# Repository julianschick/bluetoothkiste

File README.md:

# Bluetoothkiste

Bluetooth-Box für Segelflugzeuge zur Kommunikation zwischen Smartphone (mit beispielsweise XCSoar) und LX (5000/7000/7007) sowie FLARM. LX und FLARM senden über zwei getrennte Bluetooth-Module, werden also als zwei unterschiedliche Serialports auf dem Smartphone sichtbar. Das FLARM wird über den breiten RJ45-Westernstecker an die Box angeschlossen und wird auch über die Box mit Strom versorgt. Das LX wird über die 9-polige D-Sub-Schnittstelle, die meistens mit _PC_ oder _Kolibri_ beschriftet ist, angeschlossen. Eine USB-Buchse kann zusätzlich nach außen gelegt werden, um eine 5V-Stromversorgung im Cockpit zu ermöglichen. Die Datenpins sind nicht angeschlossen.

Die Verbindung zum Flarm kann über Jumper so eingestellt werden, dass keine Daten ans Flarm gesendet werden. Das ist nützlich, wenn man mehrere Bluetooth-Boxen an ein Flarm anschließen will. Die RX- und TX-Leitung zum LX kann per Jumper auf den RS232-Pins 2 und 3 frei konfiguriert werden. Das ist notwendig, da die RX-/TX-Pins vertauscht sind, je nachdem ob man die PC-Schnittstelle (u. U. mit Adapterkabel vom 5-poligen Binderstecker) oder die Kolibri-Schnittstelle verwendet. Im Zweifelsfall durchmessen, auf welchem Pin das Gerät spricht.

Ein Gehäuse, das mit dem 3D-Drucker ausgedruckt werden kann, ist ebenfalls im Repository zu finden. Bilder siehe unten.

## Teileliste

Mit passenden Artikelbezeichnungen für den Berliner Elektroteilehändler [Segor](https://www.segor.de).

Anzahl | Beschreibung | Segor-Artikelbezeichnung
--|--|--
1 | Gehäuse | *PP41 sw*
1 | USB-A-Buchse für Printmontage | *USB-A BU/V*
1 | RJ45-Buchse für Printmontage | *8P8C-BU/S 14mm*
1 | RS232-Converter | *MAX 232 N*
1 | D-Sub Buchse/Stecker 9-polig, Printmontage 90°, Abstand Pinreihe zu Steckerfläche 10mm | *DS09F-90°-10mm*/*DS09M-90°-10mm*
1 | Schaltregler | *R-78 5.0-1.0* oder (günstiger) *R-78E5.0-1.0*
1 | Sicherungshalter für Rundsicherungen, RM 5mm | *RSI-Halter/LP*
1 | Rundsicherung, RM 5mm | *RSI 2,0 A F oder RSI 2,0 A T (flink/träge)*
1 | Schraubklemmen, RM 5mm | *ARK 3 (RM 5mm)*
2 | Kondensator 10u, RM 5mm | *10u-R5.0-X7R/25V*
5 | Kondensator 1u, SMD-Bauform 1206 (3216 metrisch) | *1u0-1206-X7R/50V*
2 | Diode | *1N 5062*
2 | Bluetooth-Modul | *Bluetooth-Modul (HC-05/-06 oder ein HC-10-BLE-Modul)* [günstiger bei eBay!]
div. | Pinheader (je nach Anbringung der Bluetooth-Module)

## Wichtige Hinweise

* Je nachdem, wer zuletzt am Flugzeug rumgefrickelt hat, ist die D-Sub-Verbindung mal Male mal Female, am besten gleich das richtige Gegenstück auf die Platine löten.
* Die Bluetooth-Module können, wenn sie mit vertikalen Pinheader versehen sind, direkt reingesteckt werden (auf der Platine auch vertikale Pinheader anbringen). Sie sind dann vom Gehäusedeckel etwas vorgespannt. Bei eBay bekommt man i.d.R. Module mit 90° abgewinkelten Pinheader, diese kann man aber einfach umbiegen. Man kann sie auch direkt festlöten (ohne Female-Pinheader auf der Platine). Dabei stehen die Stifte nach unten weit aus der Platine heraus. Wenn man diese nicht abzwickt, kann man auch im Nachhinein noch per AT-Kommandos die Bluetooth-Module umkonfigurieren.
* Die Stromversorgung der Bluetooth-Module und des FLARM kann zusammengeschaltet werden per Jumper, wenn man nicht getrennt ein- und ausschalten möchte.
* Das FLARM muss extern abgesichert werden! Intern sind nur die Bluetooth-Module abgesichert.
* Darauf achten, den Schaltregler richtig herum zu montieren. Genauso den RS232-Chip.
* Darauf achten, die Bluetooth-Module richtig herum einzustecken.
* Die Bluetooth-Module müssen vor Benutzung per AT-Kommandos auf die richtige Baudrate eingestellt werden (FLARM meist 19200 und LX meist 4800). Name des Bluetoothgeräts und PIN können auch gesetzt werden. Damit man mit dem LX bidirektional kommunizieren kann, muss die Baudrate der PC-Verbindung des LX auf 4800 gesetzt werden. Das LX wirft seine NMEA-Daten immer mit 4800 Baud aus, kann aber mit konfigurierbarer Baudrate mit dem PC sprechen. Da das alles aber über das gleiche Bluetooth-Modul läuft, sollten 4800 Baud eingestellt sein.

## Bilder

## Gehäuse

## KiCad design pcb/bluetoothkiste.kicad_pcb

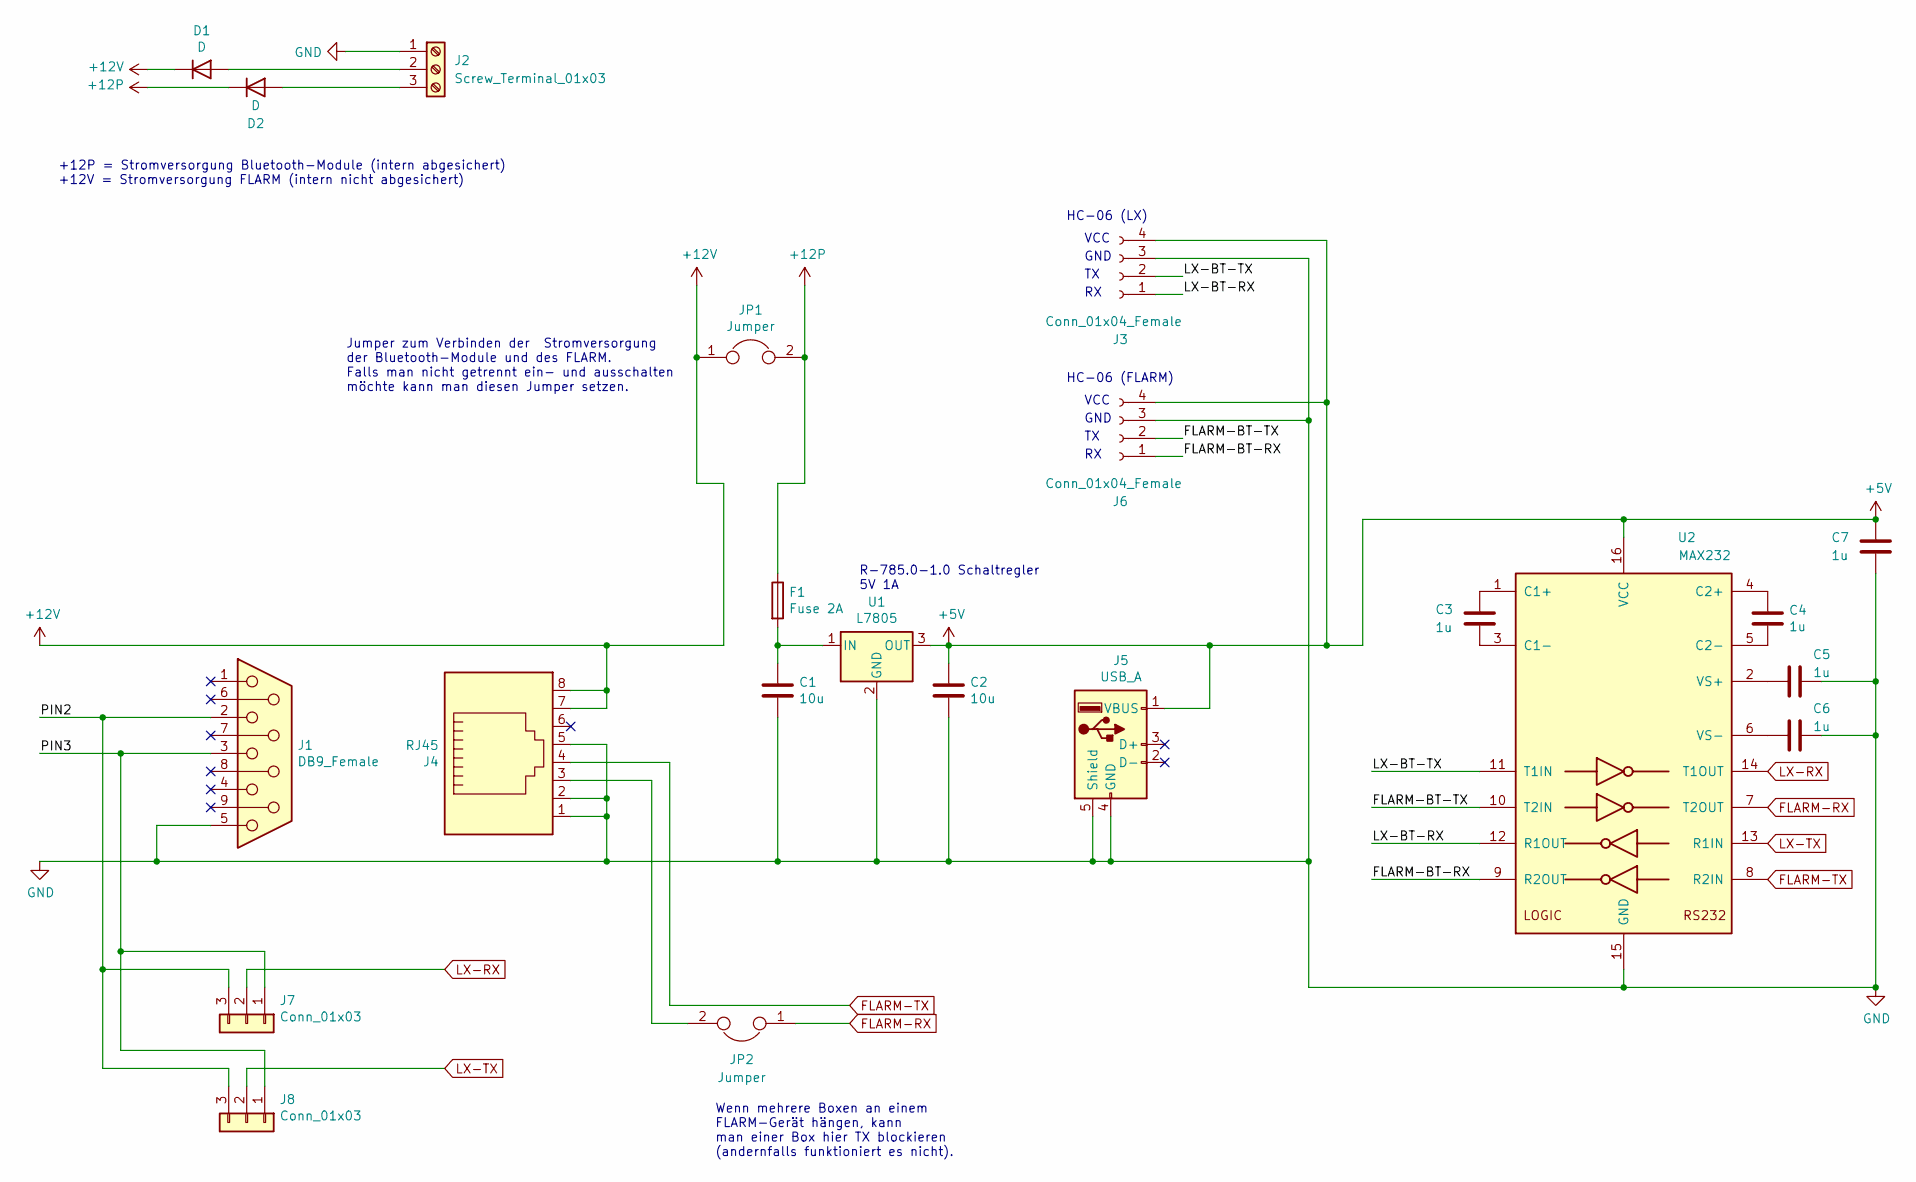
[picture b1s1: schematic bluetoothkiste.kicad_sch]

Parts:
C1, C2: 10u; C_Rect_L7.0mm_W2.0mm_P5.00mm
C3, C4, C5, C6, C7: 1u; C_1206_3216Metric_Pad1.42x1.75mm_HandSolder
D1, D2: D; D_A-405_P7.62mm_Horizontal
F1: Fuse 2A; Fuseholder_TR5_Littelfuse_No560_No460
J1: DB9_Female; DSUB-9_Female_Horizontal_Pitch2.77x2.54mm_EdgePinOffset9.40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
J2: Screw_Terminal_01x03; TerminalBlock_MetzConnect_Type055_RT01503HDWU_1x03_P5.00mm_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
J3, J6: Conn_01x04_Female; PinSocket_1x04_P2.54mm_Vertical
J4: RJ45; RJ45_SEGOR
J5: USB_A; USB_A_UPRIGHT_SEGOR
J7, J8: Conn_01x03; PinHeader_1x03_P2.54mm_Vertical
JP1, JP2: Jumper; PinHeader_1x02_P2.54mm_Vertical
U1: L7805; TO-220-3_Vertical
U2: MAX232; DIP-16_W7.62mm

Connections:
+5V: C2.1, C7.1, J3.4, J5.1 (VBUS), J6.4, U1.3 (OUT), U2.16 (VCC)
+12P: D2.1 (K), F1.1, JP1.2
+12V: D1.1 (K), J4.7, J4.8, JP1.1
/FLARM-BT-RX: J6.1, U2.9 (R2OUT)
/FLARM-BT-TX: J6.2, U2.10 (T2IN)
/LX-BT-RX: J3.1, U2.12 (R1OUT)
/LX-BT-TX: J3.2, U2.11 (T1IN)
/PIN2: J1.2, J7.3, J8.3
/PIN3: J1.3, J7.1, J8.1
FLARM-RX: JP2.1, U2.7 (T2OUT)
FLARM-TX: J4.4, U2.8 (R2IN)
GND: C1.2, C2.2, C5.1, C6.1, C7.2, J1.5, J2.1, J3.3, J4.1, J4.2, J4.5, J5.4 (GND), J5.5 (Shield), J6.3, U1.2 (GND), U2.15 (GND)
LX-RX: J7.2, U2.14 (T1OUT)
LX-TX: J8.2, U2.13 (R1IN)
unnamed: C1.1, F1.2, U1.1 (IN)
unnamed: C3.1, U2.1 (C1+)
unnamed: C3.2, U2.3 (C1-)
unnamed: C4.1, U2.4 (C2+)
unnamed: C4.2, U2.5 (C2-)
unnamed: C5.2, U2.2 (VS+)
unnamed: C6.2, U2.6 (VS-)
unnamed: D1.2 (A), J2.2
unnamed: D2.2 (A), J2.3
unnamed: J4.3, JP2.2

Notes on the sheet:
GND
HC-06 (LX)
R-785.0-1.0 Schaltregler 5V 1A
VCC
+12P = Stromversorgung Bluetooth-Module (intern abgesichert) +12V = Stromversorgung FLARM (intern nicht abgesichert)
HC-06 (FLARM)
Wenn mehrere Boxen an einem FLARM-Gerät hängen, kann man einer Box hier TX blockieren (andernfalls funktioniert es nicht).
Jumper zum Verbinden der Stromversorgung der Bluetooth-Module und des FLARM. Falls man nicht getrennt ein- und ausschalten möchte kann man diesen Jumper setzen.

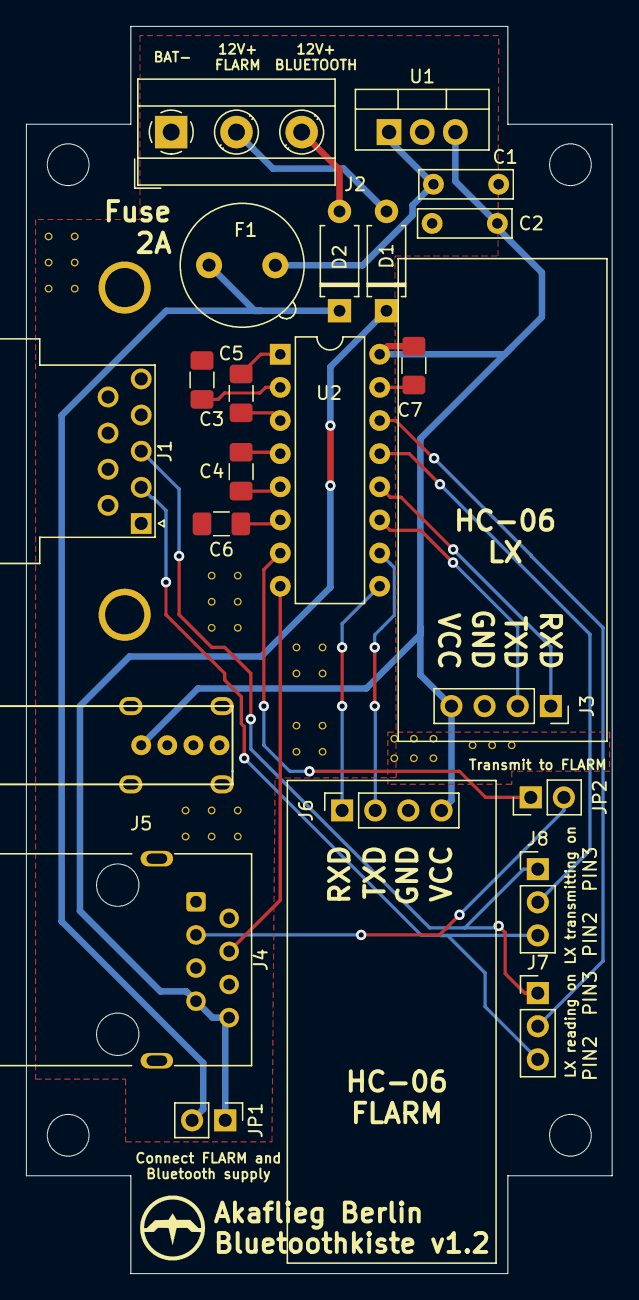
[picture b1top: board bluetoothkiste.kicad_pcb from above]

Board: 2 copper layers, 44.9 x 95.6 mm, 22 parts (0 on the bottom side), 24 nets.

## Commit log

2019-06-02 materialliste korrigiert
2019-06-02 bluetoothkiste -> pcb
2019-06-02 beschriftungen pcb
2019-06-05 pcb layout
2019-06-05 vias
2019-06-13 dual channel
2019-07-17 bugs in schematic
2019-07-17 layout updated
2019-07-17 part list updated
2019-07-30 dioden verpolungsschutz
2019-09-27 materialliste
2019-09-27 antennendistanz
2019-11-06 gerber files
2020-02-28 jumpers
2020-03-12 footprints updated
2020-03-27 readme updated
2020-04-04 images added
2020-04-04 images renamed
2020-04-04 images cropped
2020-04-05 Create LICENSE
2021-01-14 gerber v1.2
2021-11-27 bilder update
2021-12-13 case
2022-01-31 case pic added
2022-01-31 more case pics
2022-02-13 bugfix case top
2025-03-21 kicad 9
